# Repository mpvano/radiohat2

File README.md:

# RadioHat 2

This is an early version of the folder full of files that need to be installed on a raspberry pi to allow experimentation with the RadioHat version 2.0 hardware.

When downloading and installing it, ensure that it is named "radiohat2" and that it is in your home directory, or some of the shell scripts it contains will not work properly. When downloaded as a .zip archive, it may result in a folder with the branch suffix "-main" that needs to be removed if you want to use the enclosed shell scripts.

One way to create the folder on a pi is to "cd" to the directory you want it to appear in and then clone the repository using git with the command: "git clone https://github.com/mpvano/radiohat2.git". This will allow you to use all the normal git functionality.

Note also that some of the files in "docs" are very out of date or incomplete. The "Getting Started Guides" refer to a much earlier configuration with different directories on the pi and procedures to set things up. They're presented here only to give some idea what to do. I'll be replacing them with more modern versions as I get to them. RadioHat is still very much a work in progress.

### The RadioHat hardware

Unlike RadioHat 1, RadioHat2 is an open source peripheral board for the Raspberry Pi in a form similar to an extended Pi "hat". Note that this board overhangs the pi USB and Ethernet connectors to match the dimensions of the Pi itself. This means it does not qualify as an official "HAT". It is intended to be a module containing many of the devices that are commonly needed to implement 3-30Mhz radio transmitters and receivers. It may also be used with other micro-controllers that support I2S if they are sufficiently powerful to handle the needed DSP operations.

It contains the following devices:<ol>
	<li>A Freescale SGTL5000 24 bit full duplex 48Khz I2S Audio codec with headset interface</li>
	<li>A Quadrature Switched Demodulator preceded by a 3-32Mhz Band Pass Filter</li>
	<li>A Quadrature Switched Modulator followed by a 32Mhz Low Pass Filter</li>
	<li>An Si5351 I2C controlled clock oscillator configured to provide quadrature clocks for them</li>
	<li>The EEPROM required by the Pi Foundation for "hat" devices</li>
	<li>Three relay controlled low pass filters intended for use after the Modulator to reduce harmonics before an external power amplifier.</li>
 	<li>A Class A Predriver to improve the Modulator drive capabilities and to compensate for filter losses.</li>
	<li>On board analog regulators to provide cleaner power from an optional external source</li>
</ol>

These devices are wired together in the usual way needed for HF radio operation with DSP provided by the Raspberry Pi. For typical operation as a radio transceiver you still need to provide a power amplifier with output filters and a transmit/receive switching mechanism. The usual output low pass filters are adequate for most uses as input filters for the receiver if the T/R switching is done in such a way that they remain inline with the receiver.

The repository now contains another board design of the same size in FAB/txfilters1 which implements a 5 filter LPF/VSWR Meter/TR Relay for stacking with the RadioHat board. Together with your choice of power amplifier this now allows a complete transceiver to be built easily.

Note that the real time clock option and Codec Line input output connection points that were present in Radiohat 1 have been removed. The Radiohat 1 board whose Kicad Folder is still in the repository remains software compatible with this board and although it is no longer under development it remains a viable option for those needing a true "hat" for the pi, or requiring a real time clock. 

There are two different Kicad folders available for RadioHat 2 - they differ primarily in that the one named "radiohat2_QFP32" is compatible with older 32 pin versions of the codec chip instead of the current 20 pin part. They will eventually be merged into a single version.

### Fabrication of boards
RadioHat2 is open sourced hardware licensed via an MIT license and the Gerber files, preliminary BOM and some draft documentation are all part of the project. 

Although a small production run was completed to provide a few boards for use by software developers, there is currently no way to obtain boards other than ordering them from a board manufacturer yourself - this is easy and inexpensive to do and the needed Gerber files are in this repository.

Note that this board is very compact and built with QFPn and 0603 components. It's not very practical to attempt assembly by hand. The board is intended to be reflow soldered after the components are placed on pads with the help of a front side solder paste screen.

### Software
The provided software is a collection of example and test programs that demonstrate operation of the board and allow testing and troubleshooting of it. They are only intended as a starting point for more serious software development. Experimental support is also provided for use with the popular "Quisk" Transceiver software as well.

This repository is newly setup and is still being tested. There may be some issues with missing files, etc. They are being addressed as quickly as possible.

### Dependencies
In general they are confined to the normal Raspberry Pi build tools, with the exception of ncurses and its development tools.

There is a simple installation described in the PDF file in the DOC folder.

Version 7 of Kicad or later is needed to modify the board design.

### Mailing list

There is a moderated mailing list for discussing this project at https://groups.io/g/RadioHat. This project's goal is develop radio equipment that requires a valid radio amateur operator's license to operate. Please include your valid station call sign in requests to join the list, and the nature of your interest in the project.

Mario Vano
AE0GL

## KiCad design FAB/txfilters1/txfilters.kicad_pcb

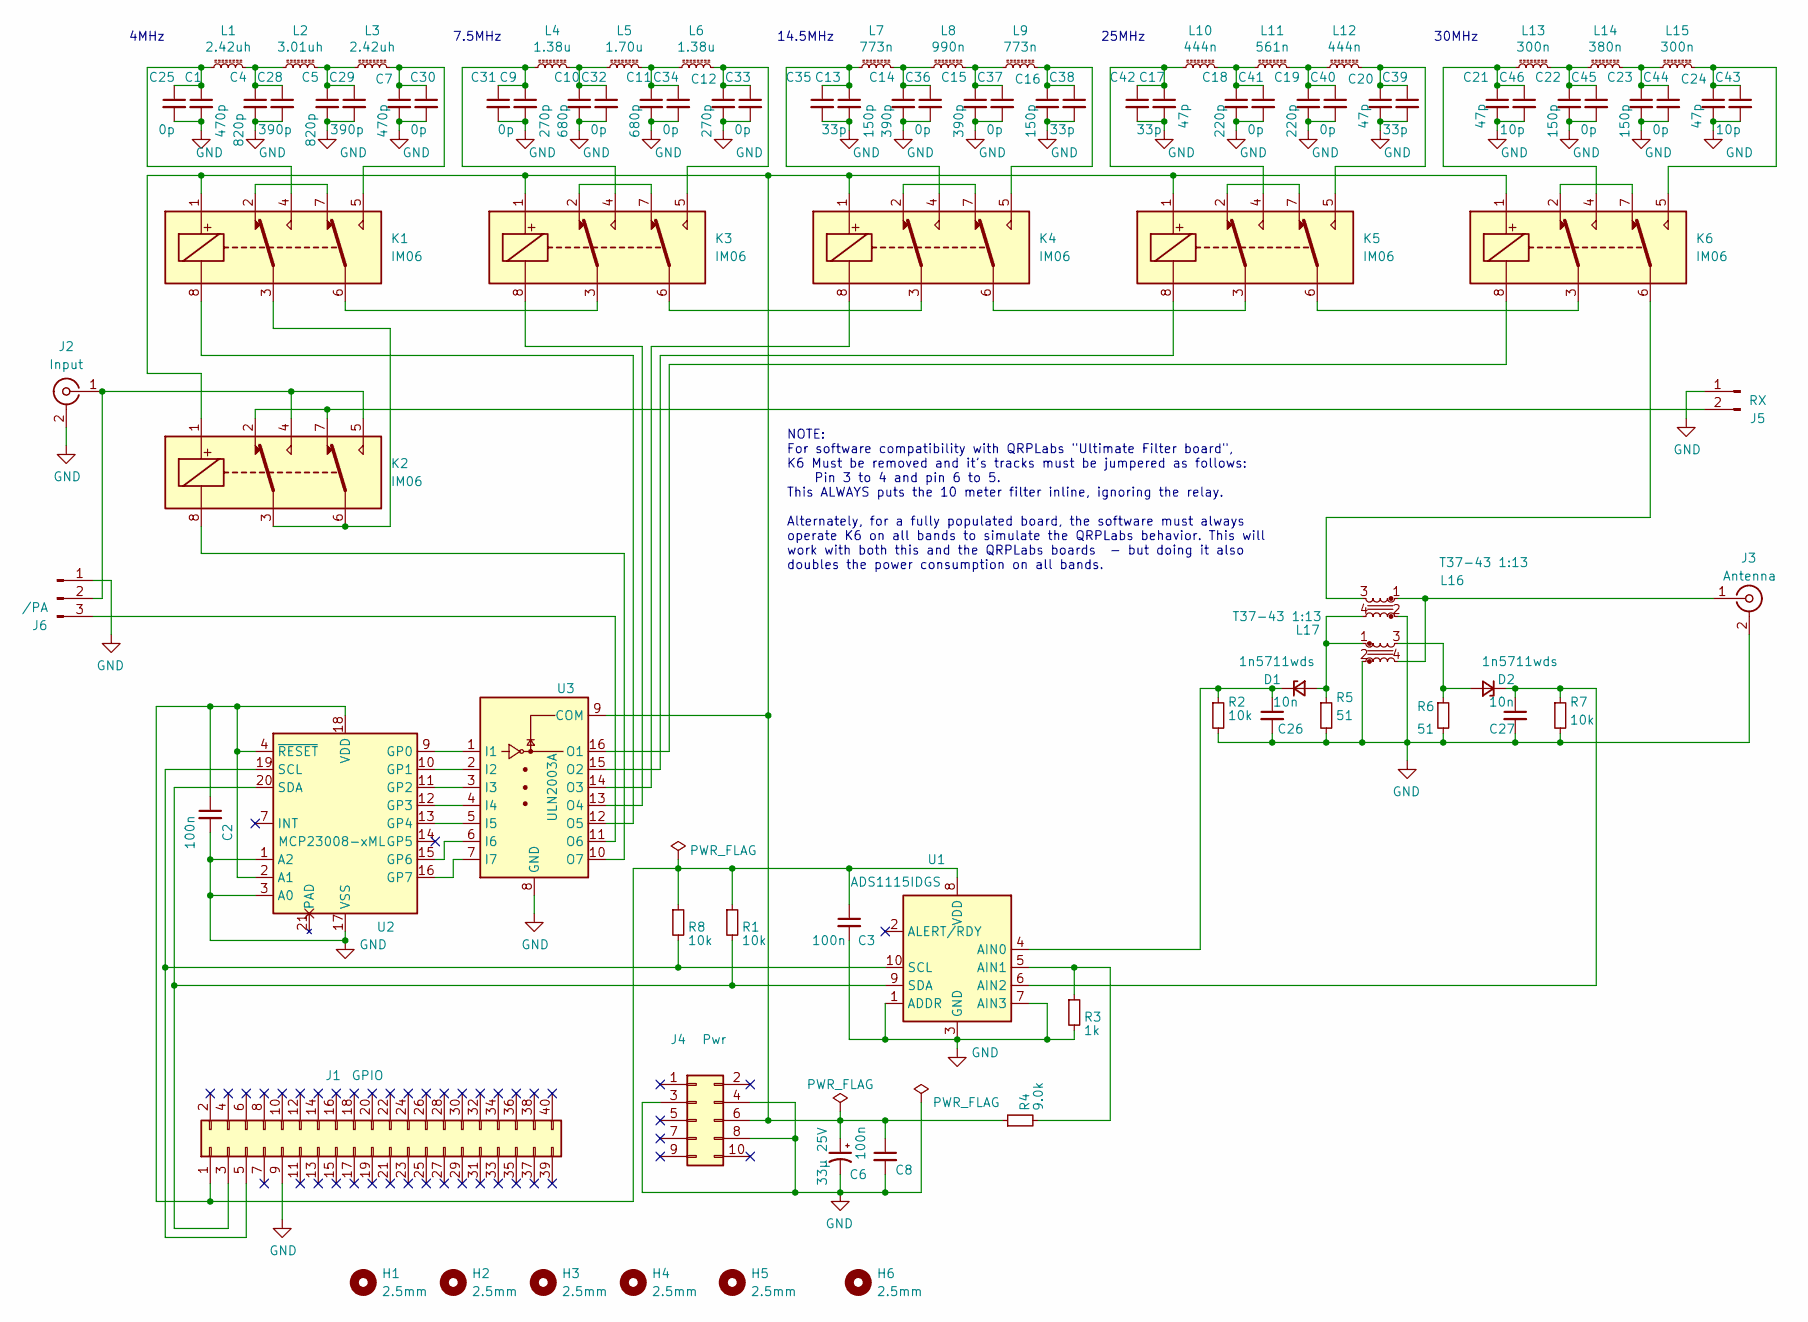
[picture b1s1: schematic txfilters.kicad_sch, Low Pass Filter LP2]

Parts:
C1, C7: 470p; C_1206_3216Metric; Manufacturer_Part_Number KGM31VCG2D471JU; DigiKey Part Number 478-KGM31VCG2D471JUCT-ND
C2, C3, C8: 100n; C_0603_1608Metric; Manufacturer_Part_Number CL10B104JB8NNNC; DigiKey Part Number 1276-1033-1-ND
C4, C5: 820p; C_1206_3216Metric; Manufacturer_Part_Number KGM31VCG2D821JU; DigiKey Part Number 478-KGM31VCG2D821JUCT-ND
C6: 33µ 25V; C_Elec_5x5.8; Manufacturer_Part_Number EEE-FK1E330UR; DigiKey Part Number PCE3802CT-ND
C9, C12: 270p; C_1206_3216Metric; Manufacturer_Part_Number KGM31BCG2D271JT; DigiKey Part Number 478-KGM31BCG2D271JTCT-ND
C10, C11: 680p; C_1206_3216Metric; Manufacturer_Part_Number KGM31VCG2D681JU; DigiKey Part Number 478-KGM31VCG2D681JUCT-ND
C13, C16, C22, C23: 150p; C_1206_3216Metric; Manufacturer_Part_Number KGM31BCG2D151JT; DigiKey Part Number 478-KGM31BCG2D151JTCT-ND
C14, C15, C28, C29: 390p; C_1206_3216Metric; Manufacturer_Part_Number KGM31BCG2D391JT; DigiKey Part Number 478-KGM31BCG2D391JTCT-ND
C17, C20, C21, C24: 47p; C_1206_3216Metric; Manufacturer_Part_Number KGM31BCG2D470JT; DigiKey Part Number 478-KGM31BCG2D470JTCT-ND
C18, C19: 220p; C_1206_3216Metric; Manufacturer_Part_Number KGM31BCG2D221JT; DigiKey Part Number 478-KGM31BCG2D221JTCT-ND
C25, C30, C31, C32, C33, C34, C36, C37, C40, C41, C44, C45: 0p; C_1206_3216Metric
C26, C27: 10n; C_0603_1608Metric; Manufacturer_Part_Number Samsung Electro-Mechanics; DigiKey Part Number 1276-1091-1-ND
C35, C38, C39, C42: 33p; C_1206_3216Metric; Manufacturer_Part_Number KGM31BCG2D330JT; DigiKey Part Number 478-KGM31BCG2D330JTCT-ND
C43, C46: 10p; C_1206_3216Metric; Manufacturer_Part_Number KGM31BCG2D100JT; DigiKey Part Number 478-KGM31BCG2D100JTCT-ND
D1, D2: 1n5711wds; D_SOD-323; Manufacturer_Part_Number 1N5711WS-7-F; DigiKey Part Number 1N5711WS-FDICT-ND
H1, H2, H3, H4, H5, H6: 2.5mm; MountingHole_2.7mm_M2.5_KA
J1: GPIO; PinSocket_2x20_P2.54mm_Vertical
J2: Input; SMA_Amphenol_132289_EdgeMount
J3: Antenna; SMA_Amphenol_132289_EdgeMount
J4: Pwr; PinSocket_2x05_P2.54mm_Vertical
J5: RX; JST_XH_B2B-XH-A_1x02_P2.50mm_Vertical
J6: /PA; JST_XH_B3B-XH-A_1x03_P2.50mm_Vertical
K1, K2, K3, K4, K5, K6: IM06; Relay_DPDT_AXICOM_IMSeries_Pitch5.08mm; Manufacturer_Part_Number 2-1462037; DigiKey Part Number PB1096-ND
L1, L3: 2.42uh; L_Toroid_Vertical_L14.0mm_W6.3mm_P4.57mm_Pulse_A
L2: 3.01uh; L_Toroid_Vertical_L14.0mm_W6.3mm_P4.57mm_Pulse_A
L4, L6: 1.38u; L_Toroid_Vertical_L14.0mm_W6.3mm_P4.57mm_Pulse_A
L5: 1.70u; L_Toroid_Vertical_L14.0mm_W6.3mm_P4.57mm_Pulse_A
L7, L9: 773n; L_Toroid_Vertical_L14.0mm_W6.3mm_P4.57mm_Pulse_A
L8: 990n; L_Toroid_Vertical_L14.0mm_W6.3mm_P4.57mm_Pulse_A
L10, L12: 444n; L_Toroid_Vertical_L14.0mm_W6.3mm_P4.57mm_Pulse_A
L11: 561n; L_Toroid_Vertical_L14.0mm_W6.3mm_P4.57mm_Pulse_A
L13, L15: 300n; L_Toroid_Vertical_L14.0mm_W6.3mm_P4.57mm_Pulse_A
L14: 380n; L_Toroid_Vertical_L14.0mm_W6.3mm_P4.57mm_Pulse_A
L16, L17: T37-43 1:13; Transformer_Toroid_Horizontal_D9.0mm_Amidon-T30
R1, R2, R7, R8: 10k; R_0603_1608Metric; Manufacturer_Part_Number RMCF0603FT10K0; DigiKey Part Number RMCF0603FT10K0CT-ND
R3: 1k; R_0603_1608Metric; Manufacturer_Part_Number RMCF0603FT1K00; DigiKey Part Number RMCF0603FT1K00CT-ND
R4: 9.0k; R_0603_1608Metric; Manufacturer_Part_Number RMCF0603FT9K09; DigiKey Part Number RMCF0603FT9K09CT-ND
R5, R6: 51; R_0603_1608Metric; Manufacturer_Part_Number RMCF0603FT51R0; DigiKey Part Number RMCF0603FT51R0CT-ND
U1: ADS1115IDGS; TSSOP-10_3x3mm_P0.5mm; Manufacturer_Part_Number ADS1115IDGSR; DigiKey Part Number 296-38849-1-ND
U2: MCP23008-xML; QFN-20-1EP_4x4mm_P0.5mm_EP2.7x2.7mm; Manufacturer_Part_Number MCP23008T-E/ML; DigiKey Part Number MCP23008T-E/MLCT-ND
U3: ULN2003A; SOIC-16_3.9x9.9mm_P1.27mm; Manufacturer_Part_Number ULN2003A; DigiKey Part Number 4518-ULN2003ACT-ND

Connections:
GND: C1.2, C2.2, C3.2, C4.2, C5.2, C6.2, C7.2, C8.2, C9.2, C10.2, C11.2, C12.2, C13.2, C14.2, C15.2, C16.2, C17.2, C18.2, C19.2, C20.2, C21.2, C22.2, C23.2, C24.2, C25.2, C26.2, C27.2, C28.2, C29.2, C30.2, C31.2, C32.2, C33.2, C34.2, C35.2, C36.2, C37.2, C38.2, C39.2, C40.2, C41.2, C42.2, C43.2, C44.2, C45.2, C46.2, J1.9, J2.2 (Ext), J3.2 (Ext), J4.3, J4.4, J4.8, J5.1, J6.1, L16.2, L17.2, R2.2, R3.2, R5.2, R6.2, R7.2, U1.1 (ADDR), U1.3 (GND), U1.7 (AIN3), U2.1 (A2), U2.3 (A0), U2.17 (VSS), U3.8 (GND)
unnamed: C1.1, C25.1, K1.4, L1.2
unnamed: C10.1, C32.1, L4.1, L5.2
unnamed: C11.1, C34.1, L5.1, L6.2
unnamed: C12.1, C33.1, K3.5, L6.1
unnamed: C13.1, C35.1, K4.4, L7.2
unnamed: C14.1, C36.1, L7.1, L8.2
unnamed: C15.1, C37.1, L8.1, L9.2
unnamed: C16.1, C38.1, K4.5, L9.1
unnamed: C17.1, C42.1, K5.4, L10.2
unnamed: C18.1, C41.1, L10.1, L11.2
unnamed: C19.1, C40.1, L11.1, L12.2
unnamed: C20.1, C39.1, K5.5, L12.1
unnamed: C21.1, C46.1, K6.4, L13.2
unnamed: C22.1, C45.1, L13.1, L14.2
unnamed: C23.1, C44.1, L14.1, L15.2
unnamed: C24.1, C43.1, K6.5, L15.1
unnamed: C4.1, C28.1, L1.1, L2.2
unnamed: C5.1, C29.1, L2.1, L3.2
unnamed: C7.1, C30.1, K1.5, L3.1
unnamed: C9.1, C31.1, K3.4, L4.2
unnamed: D1.2 (A), L16.4, L17.1, R5.1
unnamed: C26.1, D1.1 (K), R2.1, U1.4 (AIN0)
unnamed: D2.2 (A), L17.3, R6.1
unnamed: C27.1, D2.1 (K), R7.1, U1.6 (AIN2)
unnamed: C2.1, C3.1, J1.1, R1.1, R8.1, U1.8 (VDD), U2.2 (A1), U2.4 (~RESET), U2.18 (VDD)
unnamed: J1.3, R1.2, U1.9 (SDA), U2.20 (SDA)
unnamed: J1.5, R8.2, U1.10 (SCL), U2.19 (SCL)
unnamed: J2.1 (In), J6.2, K2.4, K2.5
unnamed: J3.1 (In), L16.1, L17.4
unnamed: C6.1, C8.1, J4.6, K1.1, K2.1, K3.1, K4.1, K5.1, K6.1, R4.1, U3.9 (COM)
unnamed: J5.2, K2.2, K2.7
unnamed: J6.3, U3.11 (O6)
unnamed: K1.2, K1.7
unnamed: K1.3, K2.3, K2.6
unnamed: K1.6, K3.3
unnamed: K3.2, K3.7
unnamed: K3.6, K4.3
unnamed: K4.2, K4.7
unnamed: K4.6, K5.3
unnamed: K5.2, K5.7
unnamed: K5.6, K6.3
unnamed: K6.2, K6.7
unnamed: K6.6, L16.3
unnamed: R3.1, R4.2, U1.5 (AIN1)
unnamed: U2.9 (GP0), U3.1 (I1)
unnamed: U2.10 (GP1), U3.2 (I2)
unnamed: U2.11 (GP2), U3.3 (I3)
unnamed: U2.12 (GP3), U3.4 (I4)
unnamed: U2.13 (GP4), U3.5 (I5)
unnamed: U2.15 (GP6), U3.6 (I6)
unnamed: U2.16 (GP7), U3.7 (I7)
unnamed: K6.8, U3.16 (O1)
unnamed: K5.8, U3.15 (O2)
unnamed: K4.8, U3.14 (O3)
unnamed: K3.8, U3.13 (O4)
unnamed: K1.8, U3.12 (O5)
unnamed: K2.8, U3.10 (O7)

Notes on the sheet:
30MHz
7.5MHz
25MHz
4MHz
14.5MHz
NOTE: For software compatibility with QRPLabs "Ultimate Filter board", K6 Must be removed and it's tracks must be jumpered as follows: Pin 3 to 4 and pin 6 to 5. This ALWAYS puts the 10 meter filter inline, ignoring the relay. Alternately, for a fully populated board, the software must always opera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

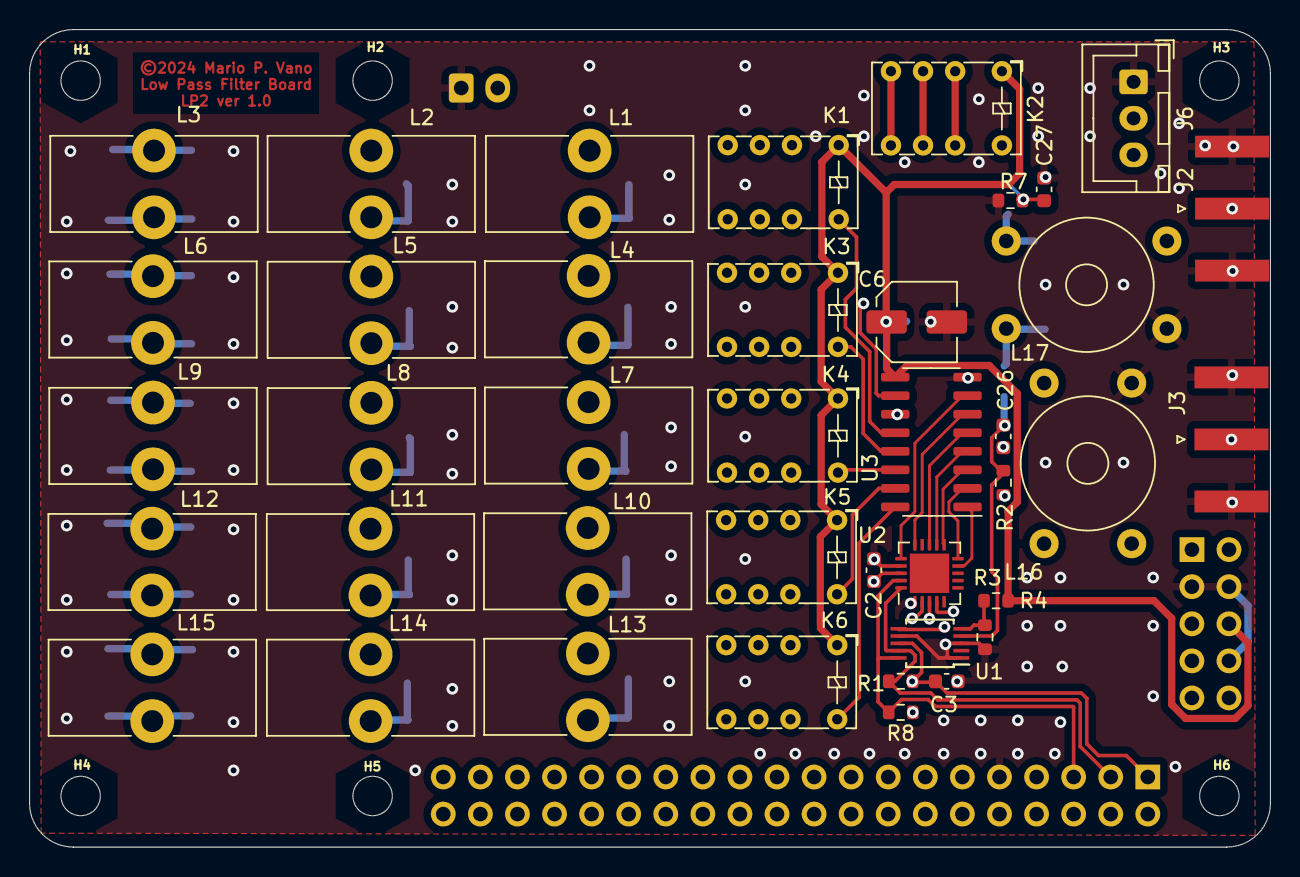
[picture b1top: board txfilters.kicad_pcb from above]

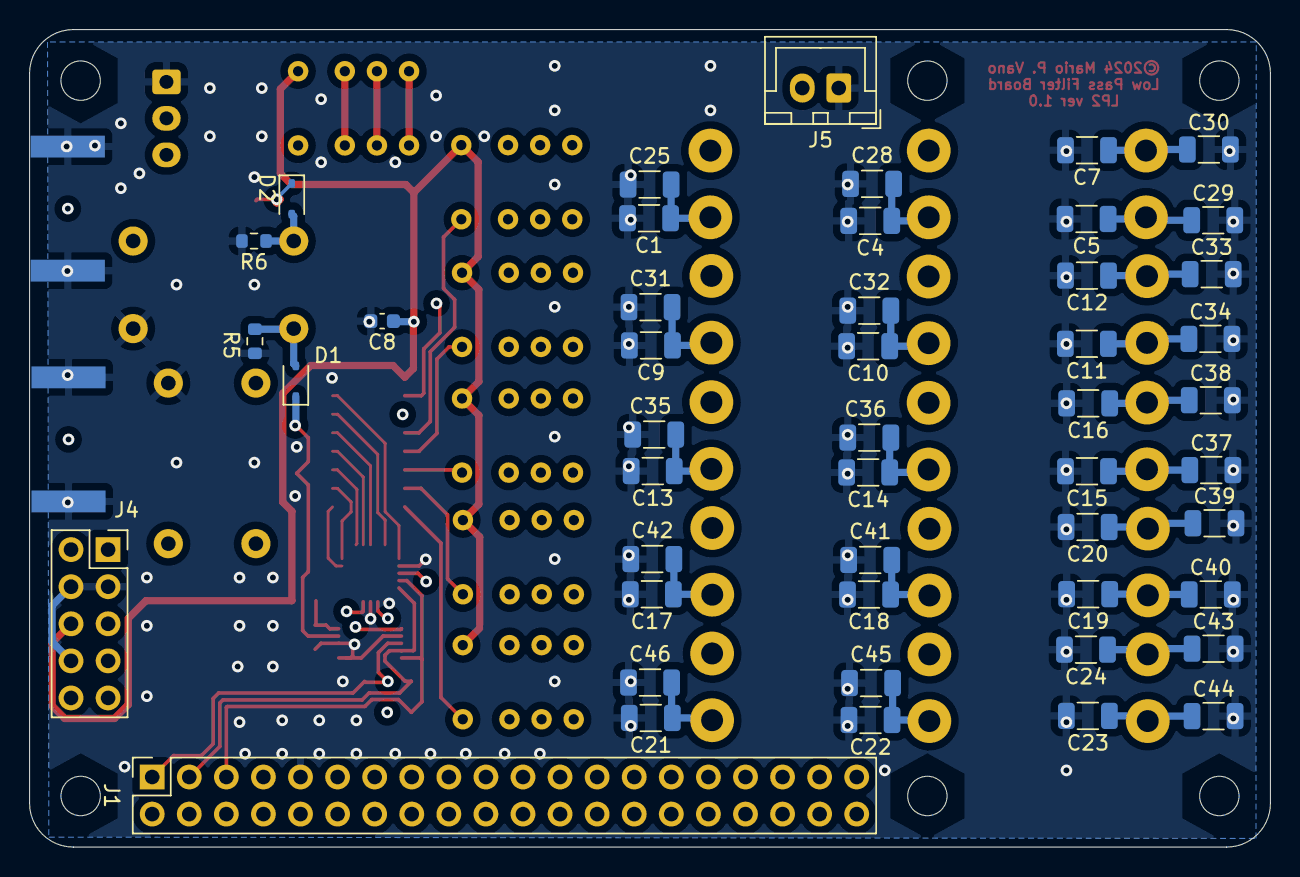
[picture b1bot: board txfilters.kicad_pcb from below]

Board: 4 copper layers, 85.0 x 56.0 mm, 94 parts (48 on the bottom side), 58 nets.

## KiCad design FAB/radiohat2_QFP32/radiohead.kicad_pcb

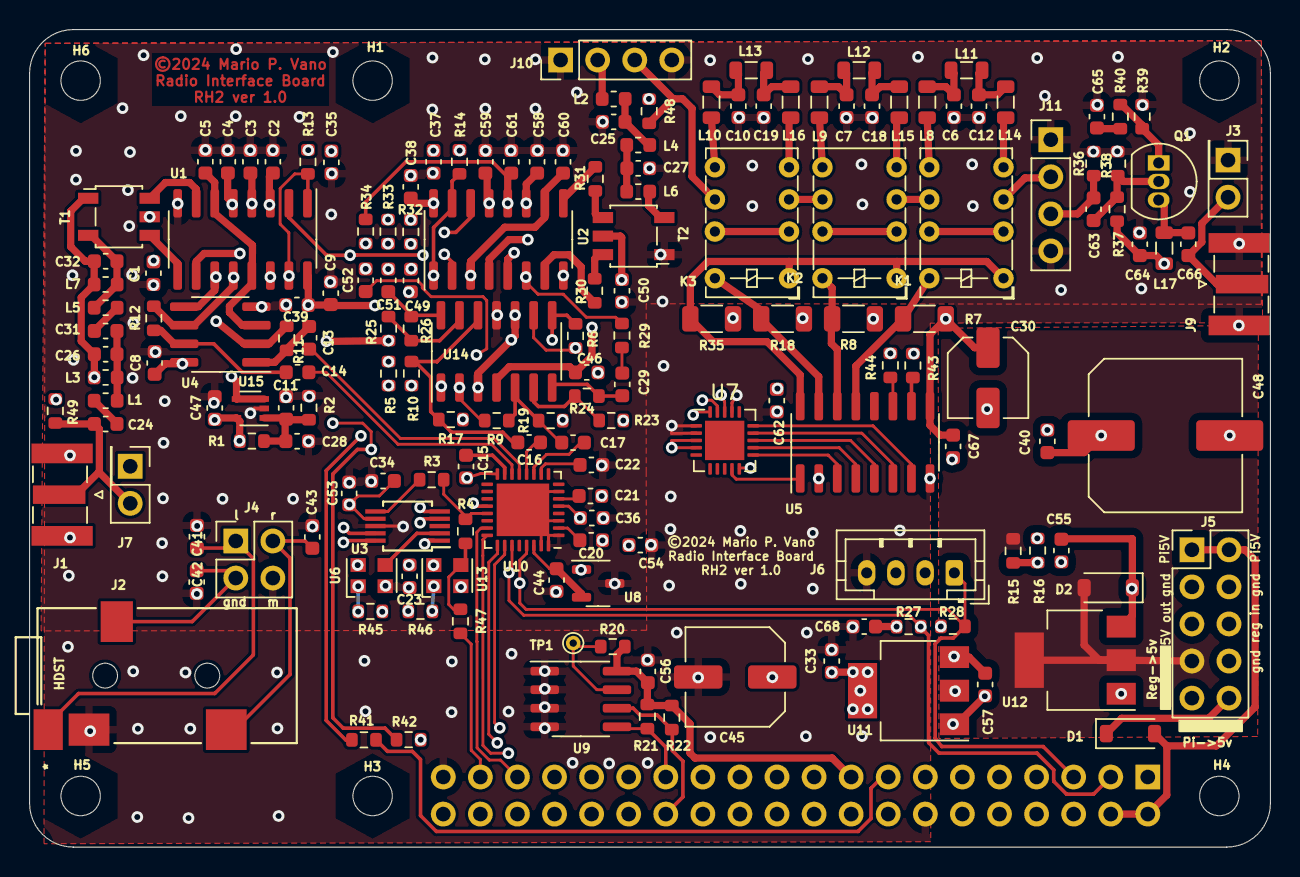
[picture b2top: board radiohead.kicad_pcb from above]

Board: 4 copper layers, 85.0 x 56.0 mm, 175 parts (1 on the bottom side), 124 nets.

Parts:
C1, C50: 10n; C_0603_1608Metric
C2, C3, C4, C5: 470n; C_0603_1608Metric
C6, C12: 200p; C_0603_1608Metric
C7, C18: 360p; C_0603_1608Metric
C8, C9, C22, C23, C28, C33, C34, C35, C36, C37, C38, C39, C46, C47, C54, C55, C56, C57, C62, C63, C64, C66, C67, C68: 100n; C_0603_1608Metric
C10, C19: 750p; C_0603_1608Metric
C11, C29, C40, C49, C51, C52, C53: 10µ; C_0603_1608Metric
C13, C14, C15, C16, C17, C20, C21, C44: 1µ; C_0603_1608Metric
C24, C31: 620p; C_0603_1608Metric
C25, C27: 130p; C_0603_1608Metric
C26, C32: 180p; C_0603_1608Metric
C30: 33µ 25V; C_Elec_5x5.8
C41, C42, C43, C65: 1n; C_0603_1608Metric
C45: 100µ 5V; C_Elec_6.3x5.4
C48: 1500µ 6.3V; C_Elec_10x10.2
C58, C59, C60, C61: 22n; C_0603_1608Metric
D1, D2: 20V 500MA; D_SOD-123
H1, H2, H3, H4, H5, H6: 2.5mm; MountingHole_2.7mm_M2.5_KA
J1: RF In; SMA_Samtec_SMA-J-P-X-ST-EM1_EdgeMount
J2: HDST; SJ-43514TS-SMT
J3: RF out; PinHeader_2x01_P2.54mm_Vertical
J4: Headset; PinHeader_2x02_P2.54mm_Vertical
J5: Power; PinHeader_2x05_P2.54mm_Vertical
J6: STEMMA I2C; JST_PH_B4B-PH-K_1x04_P2.00mm_Vertical
J7: RF In; PinHeader_2x01_P2.54mm_Vertical
J8: Raspberry Pi GPIO; PinSocket_2x20_P2.54mm_Vertical
J9: RF out B; SMA_Samtec_SMA-J-P-X-ST-EM1_EdgeMount
J10: QSD | LPF; PinHeader_1x04_P2.54mm_Vertical
J11: LPF | PA; PinHeader_1x04_P2.54mm_Vertical
K1, K2, K3: IM43; Relay_DPDT_AXICOM_IMSeries_Pitch5.08mm
L1, L2, L5, L6: 470n; L_0603_1608Metric
L3, L7: 1µ5; L_0603_1608Metric
L4: 560n; L_0603_1608Metric
L8, L14: 560n; L_0805_2012Metric
L9, L11, L15: 820n; L_0805_2012Metric
L10, L12, L16: 1µ5; L_0805_2012Metric
L13: 2µ7; L_0805_2012Metric
L17: 40µ; L_0805_2012Metric
Q1: PN2222A; TO-92_Inline
R1: 12k; R_0603_1608Metric
R2, R24, R26: 20k; R_0603_1608Metric
R3, R4, R41, R42, R43, R44, R47, R48, R49: 0r; R_0603_1608Metric
R5, R6: 30k; R_0603_1608Metric
R7, R8, R18, R35: 350R; R_1206_3216Metric
R9, R10, R11, R12, R13, R14, R17, R19, R23, R25, R27, R28, R45, R46: 10k; R_0603_1608Metric
R15: 333r; R_0603_1608Metric
R16, R20: 1k; R_0603_1608Metric
R21, R22: 3k9; R_0603_1608Metric
R29, R30, R31, R32, R33, R34, R36, R39: 50R; R_0603_1608Metric
R37: 2k2; R_0603_1608Metric
R38: 450R; R_0603_1608Metric
R40: 68R; R_0603_1608Metric
T1, T2: MABAES0031; Transformer_MACOM_MABAES00031CT
TP1: /Write; TestPoint_THTPad_D1.0mm_Drill0.5mm
U1, U2: SN74CBT3253; SOIC-16_3.9x9.9mm_P1.27mm
U3: Si5351A-B-GT; MSOP-10_3x3mm_P0.5mm
U4: LM4562; SOIC-8_3.9x4.9mm_P1.27mm
U5: ULN2003A; SOIC-16_3.9x9.9mm_P1.27mm
U6: tcxo 25.0Mhz; Oscillator_SMD_Kyocera_KC2520Z-4Pin_2.5x2.0mm
U7: MCP23008-xML; QFN-20-1EP_4x4mm_P0.5mm_EP2.7x2.7mm
U8: ap7313; SOT-23-3
U9: CAT24C128; SOIC-8_3.9x4.9mm_P1.27mm
U10: SGTL5000XNAA3; QFN-32-1EP_5x5mm_P0.5mm_EP3.6x3.6mm
U11: LD1117S33TR_SOT223; SOT-223-3_TabPin2
U12: LM317_SOT-223; SOT-223-3_TabPin2
U13: txco 12.288Mhz; Oscillator_SMD_Kyocera_KC2520Z-4Pin_2.5x2.0mm
U14: TLV9064; SO-14_3.9x8.65mm_P1.27mm
U15: TLV9001IDCK; SOT-353_SC-70-5

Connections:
+3V3: C56.1, C68.1, J6.3, J8.1, J8.17, R20.2, R21.2, R22.2, R27.2, R28.2, U9.8 (VCC)
+5V: C8.1, C9.1, C38.1, C39.1, C40.2, C46.1, C48.1, C57.1, J5.5, J5.9, U1.16 (VCC), U2.16 (VCC), U4.8 (V+), U11.3 (VI), U14.4 (V+)
+12V: C30.1, C55.1, C64.1, C67.1, D2.1 (K), J5.6, L17.1, R7.1, R8.1, R18.1, R35.1, R37.1, U5.9 (COM), U12.3 (VI)
/T_MCLK: J8.37, R47.2
BIAS2V: C1.1, C50.1, R17.1, R19.2, R23.2, R25.2, T1.2, T2.2, U14.3 (+), U14.10 (+), U15.3 (-), U15.4
CODEC-DIN: J8.40, U10.26 (I2S_DIN)
CODEC-DOUT: J8.38, U10.25 (I2S_DOUT)
CODEC-LRCLK: J8.35, U10.23 (I2S_LRCLK)
CODEC-SCLK: J8.12, U10.24 (I2S_SCLK)
CODEC_MCLK: R3.2, R4.2, U10.21 (SYS_MCLK)
GND: C1.2, C2.2, C3.2, C4.2, C5.2, C6.2, C7.2, C8.2, C9.2, C10.2, C11.2, C12.2, C18.2, C19.2, C22.1, C23.1, C25.2, C27.2, C28.2, C30.2, C33.2, C34.2, C35.2, C36.2, C37.2, C38.2, C39.2, C40.1, C41.1, C42.1, C43.1, C44.1, C45.2, C46.2, C47.2, C48.2, C50.2, C53.1, C54.2, C55.2, C56.2, C57.2, C58.2, C59.2, C60.2, C61.2, C62.2, C64.2, C65.2, C67.2, C68.2, J2.4, J3.1, J4.4, J5.3, J5.4, J5.8, J6.4, J8.6, J8.9, J8.14, J8.20, J8.25, J8.30, J8.34, J8.39, J9.2 (Ext), J10.1, J10.4, J11.1, J11.4, R2.1, R16.2, R36.2, R38.2, R39.2, T2.4, U1.8 (GND), U2.8 (GND), U3.8 (GND), U4.4 (V-), U5.8 (GND), U6.2 (GND), U7.1 (A2), U7.2 (A1), U7.17 (VSS), U8.3 (GND), U9.1 (A0), U9.2 (A1), U9.3 (A2), U9.4 (GND), U10.1 (GND), U10.3 (GND), U10.7 (AGND), U10.31 (CTRL_ADR0_CS), U10.32 (CTRL_MODE), U10.33 (GND), U11.1 (GND), U13.2 (GND), U14.11 (V-), U15.2 (V-)
HPL: C21.1, C43.2, J2.2, J4.2
HPR: C20.1, C41.2, J2.3, J4.3
I2C-SCL: J6.1, J8.5, R28.1, U3.4 (SCL), U7.19 (SCL), U10.29 (CTRL_CLK)
I2C-SDA: J6.2, J8.3, R27.1, U3.5 (SDA), U7.20 (SDA), U10.27 (CTRL_DATA)
LINEIN-L: C14.1, U10.14 (LINEIN_L)
LINEIN-R: C13.2, U10.13 (LINEIN_R)
LINEOUT_L: C16.1, R10.1, R17.2, U14.12 (+)
LINEOUT_R: C17.2, R9.1, R19.1, U14.5 (+)
MIC-IN: C15.1, C42.2, J2.1, J4.1, U10.16 (MIC_BIAS)
unnamed: C6.1, L8.1, L11.2
unnamed: C7.1, L9.1, L12.2
unnamed: C10.1, L10.1, L13.2
unnamed: C12.1, L11.1, L14.1
unnamed: C13.1, R11.1, U4.1
unnamed: C14.2, R12.1, U4.7
unnamed: C18.1, L12.1, L15.1
unnamed: C19.1, L13.1, L16.1
unnamed: C24.1, L1.2
unnamed: C25.1, L2.1, L4.2
unnamed: C26.1, C31.2, L1.1, L3.1
unnamed: C27.1, L4.1, L6.2
unnamed: C29.1, R24.2, U14.7
unnamed: C29.2, R29.1
unnamed: C31.1, L5.2
unnamed: C32.1, L5.1, L7.1, T1.5
unnamed: C49.1, R5.2, U14.1
unnamed: C49.2, R32.1
unnamed: C51.1, R26.2, U14.14
unnamed: C51.2, R33.1
unnamed: C52.1, R6.2, U14.8
unnamed: C52.2, R34.1
unnamed: C65.1, R40.2
unnamed: D1.2 (A), J5.1, J5.2, J8.2, J8.4
unnamed: D1.1 (K), J5.10
unnamed: D2.2 (A), J5.7, R15.1, U12.2 (VO)
unnamed: C26.2, C32.2, J1.2 (Ext), J7.1, L3.2, L7.2, T1.4
unnamed: C24.2, J1.1 (In), J7.2, R49.1
unnamed: C66.2, J3.2, J9.1 (In)
unnamed: J8.15, R41.2
unnamed: J8.16, R42.2
unnamed: J8.27, R21.1, U9.5 (SDA)
unnamed: J8.28, R22.1, U9.6 (SCL)
unnamed: J10.3, K3.6, R48.2
unnamed: J11.2, K1.3
unnamed: C63.2, J11.3, R36.1
unnamed: K1.2, K1.7
unnamed: K1.4, L14.2
unnamed: K1.5, L8.2
unnamed: K1.6, K2.3
unnamed: K2.2, K2.7
unnamed: K2.4, L15.2
unnamed: K2.5, L9.2
unnamed: K2.6, K3.3
unnamed: K3.2, K3.7
unnamed: K3.4, L16.2
unnamed: K3.5, L10.2
unnamed: L6.1, T2.5
unnamed: C63.1, Q1.2 (B), R37.2, R38.1
unnamed: C66.1, L17.2, Q1.3 (C)
unnamed: Q1.1 (E), R39.1, R40.1
unnamed: R30.2, T2.1
unnamed: R31.2, T2.3
unnamed: T1.1, U1.7 (1A)
unnamed: C5.1, U1.6 (1B1), U1.13 (2B4), U4.3 (+)
unnamed: C4.1, R12.2, U1.5 (1B2), U1.12 (2B3), U4.6 (-)
unnamed: C3.1, U1.4 (1B3), U1.11 (2B2), U4.5 (+)
unnamed: C2.1, R11.2, U1.3 (1B4), U1.10 (2B1), U4.2 (-)
unnamed: T1.3, U1.9 (2A)
unnamed: R30.1, U2.7 (1A)
unnamed: C59.1, R29.2, U2.6 (1B1), U2.13 (2B4)
unnamed: C61.1, R34.2, U2.5 (1B2), U2.12 (2B3)
unnamed: C58.1, R33.2, U2.4 (1B3), U2.11 (2B2)
unnamed: C60.1, R32.2, U2.3 (1B4), U2.10 (2B1)
unnamed: R31.1, U2.9 (2A)
unnamed: R3.1, U3.6 (CLK2)
unnamed: U3.2 (XA), U6.3 (CLK)
unnamed: U5.1 (I1), U7.9 (GP0)
unnamed: U5.2 (I2), U7.10 (GP1)
unnamed: U5.3 (I3), U7.11 (GP2)
unnamed: U5.4 (I4), U7.12 (GP3)
unnamed: U5.5 (I5), U7.13 (GP4)
unnamed: U5.6 (I6), U7.14 (GP5)
unnamed: U5.7 (I7), U7.15 (GP6)
unnamed: K1.1, K2.1, K3.1, R35.2, U5.16 (O1)
unnamed: K3.8, R18.2, U5.15 (O2)
unnamed: K2.8, R8.2, U5.14 (O3)
unnamed: K1.8, R7.2, U5.13 (O4)
unnamed: R44.2, U5.11 (O6)
unnamed: R43.2, U5.10 (O7)
unnamed: R45.2, U6.1 (INH)
unnamed: R20.1, TP1.1, U9.7 (WP)
unnamed: C21.2, U10.6 (HP_L)
unnamed: C20.2, U10.2 (HP_R)
unnamed: C16.2, U10.12 (LINEOUT_L)
unnamed: C17.1, U10.11 (LINEOUT_R)
unnamed: C15.2, U10.15 (MIC)
unnamed: C22.2, U10.10 (VAG)
unnamed: C44.2, U8.2 (VO), U10.30 (VDDD)
unnamed: R15.2, R16.1, U12.1 (ADJ)
unnamed: R46.2, U13.1 (INH)
unnamed: R5.1, R9.2, U14.2 (-)
unnamed: R23.1, R24.1, U14.6 (-)
unnamed: R6.1, R10.2, U14.9 (-)
unnamed: R25.1, R26.1, U14.13 (-)
unnamed: C11.1, C28.1, R1.1, R2.2, U15.1 (+)
PRE-IN: J10.2, L2.2
RX-INBUS: R48.1, R49.2
TEENSY: R4.1, R47.1, U13.3 (CLK)
VCC: C23.2, C33.1, C34.1, C35.1, C36.1, C37.1, C45.1, C47.1, C53.2, C54.1, C62.1, R1.2, R13.2, R14.2, R45.1, R46.1, U3.1 (VDD), U3.7 (VDDO), U6.4 (VCC), U7.3 (A0), U7.4 (~RESET), U7.18 (VDD), U8.1 (VI), U10.5 (VDDA), U10.20 (VDDIO), U11.2 (VO), U13.4 (VCC), U15.5 (V+)
VFO-S0: U1.14 (S0), U2.14 (S0), U3.10 (CLK0)
VFO-S1: U1.2 (S1), U2.2 (S1), U3.9 (CLK1)
/RX-EN: R13.1, R42.1, R44.1, U1.1 (1~OE), U1.15 (2~OE)
/TX-EN: R14.1, R41.1, R43.1, U2.1 (1~OE), U2.15 (2~OE)

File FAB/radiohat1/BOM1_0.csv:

Reference, Quantity, Value, Footprint, Datasheet, Description, Height, Manufacturer_Name, Manufacturer_Part_Number, Mouser Part Number, Mouser Price/Stock
C1 C50,2,10n,Capacitor_SMD:C_0603_1608Metric,~,,,,,,
C12 C13 C14 C15 C16 C17 C18 C19 C20 C21 C30 C44,12,1m,Capacitor_SMD:C_0603_1608Metric,~,,,,,,
C8 C9 C10 C22 C23 C33 C34 C35 C36 C37 C38 C39 C46 C47 C54 C56 C57,17,100n,Capacitor_SMD:C_0603_1608Metric,~,,,,,,
C25 C27,2,130p,Capacitor_SMD:C_0603_1608Metric,~,,,,,,
C26 C32,2,180p,Capacitor_SMD:C_0603_1608Metric,~,,,,,,
C11 C28 C40 C53,4,10m,Capacitor_SMD:C_0603_1608Metric,~,,,,,,
C24 C31,2,620p,Capacitor_SMD:C_0603_1608Metric,~,,,,,,
C41 C42 C43,3,1n,Capacitor_SMD:C_0603_1608Metric,~,,,,,,
C45,1,100m,Capacitor_SMD:C_Elec_6.3x5.4,~,,,,,,
C48,1,1500m,Capacitor_SMD:C_Elec_10x10.2,~,,,,,,
C29 C49 C51 C52,4,10u,Capacitor_SMD:C_0603_1608Metric,~,,,,,,
C2 C3 C4 C5,4,470n,Capacitor_SMD:C_0603_1608Metric,~,,,,,,
C55,1,100n 25V,Capacitor_SMD:C_0603_1608Metric,~,,,,,,
C58 C59 C60 C61,4,22n,Capacitor_SMD:C_0603_1608Metric,~,,,,,,
C6 C7,2,4.7n,Capacitor_SMD:C_0603_1608Metric,~,,,,,,
D1,1,MBRA340T3G,radiohead:D_SMA-SMB_Universal_Handsoldering,https://www.onsemi.com/pub/Collateral/MBRA340T3-D.PDF,,,,,,
D2,1,MBR0520LT,Diode_SMD:D_SOD-123,http://www.onsemi.com/pub_link/Collateral/MBR0520LT1-D.PDF,,,,,,
H1 H2 H3 H4,4,2.5mm,MountingHole:MountingHole_2.7mm_M2.5,~,,,,,,
J1,1,HF IN,Connector_Coaxial:SMA_Samtec_SMA-J-P-X-ST-EM1_EdgeMount, ~,,,,,,
J2,1,HF OUT,Connector_Coaxial:SMA_Samtec_SMA-J-P-X-ST-EM1_EdgeMount, ~,,,,,,
J3,1,headset,Connector_Audio:SJ-43514TS-SMT,,,,,,,
J4,1,Headset & I/Q,Connector_PinHeader_2.54mm:PinHeader_2x05_P2.54mm_Vertical,~,,,,,,
J5,1,Power,Connector_PinHeader_2.54mm:PinHeader_2x05_P2.54mm_Vertical,~,,,,,,
J6,1,CR1220,2895:2895,https://www.mouser.com/datasheet/2/215/Keystone_Electronics_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,Coin Cell Battery Holders CR1220 COIN CELL THM RETAINER,2.95,Keystone Electronics,2895,534-2895,https://www.mouser.co.uk/ProductDetail/Keystone-Electronics/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
J7,1,I2C,Connector_JST:JST_PH_S4B-PH-SM4-TB_1x04-1MP_P2.00mm_Horizontal,~,,,,,,
J8,1,Raspberry Pi GPIO,Connector_PinSocket_2.54mm:PinSocket_2x20_P2.54mm_Vertical,~,,,,,,
JP1,1,/TX,Jumper:SolderJumper-2_P1.3mm_Bridged2Bar_Pad1.0x1.5mm,~,,,,,,
JP2,1,/RX,Jumper:SolderJumper-2_P1.3mm_Bridged2Bar_Pad1.0x1.5mm,~,,,,,,
L1 L2 L5 L6,4,470n,Inductor_SMD:L_0603_1608Metric,~,,,,,,
L3 L7,2,1µ5,Inductor_SMD:L_0603_1608Metric,~,,,,,,
L4,1,560n,Inductor_SMD:L_0603_1608Metric,~,,,,,,
R1,1,300,Resistor_SMD:R_0603_1608Metric,~,,,,,,
R9 R10 R11 R12 R13 R14 R17 R18 R19 R23 R25 R27 R28,13,10k,Resistor_SMD:R_0603_1608Metric,~,,,,,,
R15,1,333r,Resistor_SMD:R_0603_1608Metric,~,,,,,,
R2,1,200,Resistor_SMD:R_0603_1608Metric,~,,,,,,
R16 R20,2,1k,Resistor_SMD:R_0603_1608Metric,~,,,,,,
R21 R22,2,3k9,Resistor_SMD:R_0603_1608Metric,~,,,,,,
R24 R26,2,20k,Resistor_SMD:R_0603_1608Metric,~,,,,,,
R3 R4 R7 R8,4,50,Resistor_SMD:R_0603_1608Metric,~,,,,,,
R29 R30 R31 R32 R33 R34,6,50R,Resistor_SMD:R_0603_1608Metric,~,,,,,,
R35,1,0,Resistor_SMD:R_0603_1608Metric,~,,,,,,
R5 R6,2,30k,Resistor_SMD:R_0603_1608Metric,~,,,,,,
T1 T2,2,MABAES0031,radiohead:Transformer_MACOM_MABAES00031CT-HYBRID,https://cdn.macom.com/datasheets/MABAES0060.pdf,Audio Transformers / Signal Transformers .3-200MHz IL 1.5dB Impedance Ratio 1:4,3.8,MACOM,MABAES0031CT,1464-MABAES0031-CT,
TP1,1,/Write,TestPoint:TestPoint_THTPad_D1.0mm_Drill0.5mm,~,,,,,,
TP2,1,I,TestPoint:TestPoint_THTPad_D1.0mm_Drill0.5mm,~,,,,,,
TP3,1,Q,TestPoint:TestPoint_THTPad_D1.0mm_Drill0.5mm,~,,,,,,
TP4,1,MCLK,TestPoint:TestPoint_THTPad_D1.0mm_Drill0.5mm,~,,,,,,
TP5,1,-in,TestPoint:TestPoint_THTPad_D1.0mm_Drill0.5mm,~,,,,,,
TP6,1,+in,TestPoint:TestPoint_THTPad_D1.0mm_Drill0.5mm,~,,,,,,
TP7,1,-out,TestPoint:TestPoint_THTPad_D1.0mm_Drill0.5mm,~,,,,,,
TP8,1,+out,TestPoint:TestPoint_THTPad_D1.0mm_Drill0.5mm,~,,,,,,
TP9,1,RESET,TestPoint:TestPoint_THTPad_D1.0mm_Drill0.5mm,~,,,,,,
U10,1,SGTL5000XNAA3,Package_DFN_QFN:QFN-32-1EP_5x5mm_P0.5mm_EP3.7x3.7mm,https://www.nxp.com/docs/en/data-sheet/SGTL5000.pdf,,,,,,
U11,1,LD1117S33TR_SOT223,Package_TO_SOT_SMD:SOT-223-3_TabPin2,http://www.st.com/st-web-ui/static/active/en/resource/techni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,,,,,,
U12,1,LM317_SOT-223,Package_TO_SOT_SMD:SOT-223-3_TabPin2,http://www.ti.com/lit/ds/symlink/lm317.pdf,,,,,,
U1 U2,2,SN74CBT3253,Package_SO:SOIC-16_3.9x9.9mm_P1.27mm,http://www.ti.com/lit/gpn/sn74cbt3253,,,,,,
U3,1,Si5351A-B-GT,Package_SO:MSOP-10_3x3mm_P0.5mm,https://www.silabs.com/documents/public/data-sheets/Si5351-B.pdf,,,,,,
U4,1,LM4562,Package_SO:SOIC-8_3.9x4.9mm_P1.27mm,http://www.ti.com/lit/ds/symlink/lm4562.pdf,,,,,,
U5 U7,2,TLV2462CDR,Package_SO:SOIC-8_3.9x4.9mm_P1.27mm,http://www.ti.com/lit/ds/symlink/lm358.pdf,,,,,,
U6,1,DS3231MZ,Package_SO:SOIC-8_3.9x4.9mm_P1.27mm,http://datasheets.maximintegrated.com/en/ds/DS3231M.pdf,,,,,,
U8,1,ap7313-18mpv,ul_AP731318SAG7:AP7313-18SAG-7,,,,,,,
U9,1,CAT24C128,Package_SO:SOIC-8_3.9x4.9mm_P1.27mm,https://www.onsemi.com/pub/Collateral/CAT24C128-D.PDF,,,,,,
Y1,1,27Mhz,Crystal:Crystal_SMD_Abracon_ABM8G-4Pin_3.2x2.5mm,~,,,,,,

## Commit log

2024-03-22 RADIOHAT2
2024-03-22 Update .DS_Store
    Initial Upload
2024-03-22 updated readme
    updated readme info
2024-03-22 License updated
2024-03-22 polarity bug on /tx and /rx
2024-03-26 DOC updates
2024-03-26 fab files added
2024-03-26 housekeeping
2024-03-27 Update .gitignore
    pruning unneeded backups
2024-03-27 cleanup
2024-03-27 added QFP32 HW version
2024-03-27 more cleanup
2024-03-27 added transceiver example
2024-03-27 Transceiver formatting
2024-03-27 more detail added
2024-03-27 Correct signal colors
2024-03-28 FOOTPRINT ERROR WARNING
2024-04-20 vfoinit fixed on pi 5
2024-05-02 LPF Board Initial Version
    Kicad Files as sent to Fab for the LPF. VSWR Bridge and T/R Relay designed for stacking with RadioHat2
2024-05-02 updated reference transceiver
    Updated PDF of reference transceiver
2024-05-02 Update Radiohat 2 Reference Transceiver.pdf
    Brought top page reference transceiver image up to date
2024-05-04 updated ref transceiver
2024-05-05 Update vswr.cpp to fix turns ratio scaling bug
    The turns ratio coefficient was not being applied to the diode correction in the power calculations
2024-05-05 Reference Transceiver updated
    Better picture of latest case refurbishment - shows wiring details
2024-05-05 Update hardware_radiohat1.py to metering ON
2024-05-06 more VSWR fixes
    Yes, it's confusing and messy, but now the algorithm agrees with those used by all my other VSWR implementations.
2024-05-06 control.cpp: changed LPF2 limit from 25 to 23Mhz
2024-11-20 Updates from Field
    Updates to the repository based on field experiences with two Display10 reference transceivers
2024-11-22 new script for digital modes
    added socat script to allow gnuradio program "usbplus.py" to work directly with "transceiver" cat emulation and alsa redirection for fldigi and wsjtx
2024-11-26 update quisk settings samples
2024-11-27 updated cat script
2024-11-27 always use ALSA Loopback for digital
2024-12-01 added no-ui version of digital modes
2024-12-01 fix typo in tx filter block
2024-12-14 Added experimental keyer
    An experimental Keyer written in Python was added

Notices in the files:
FAB/radiohat2_QFP32/radiohead.kicad_pcb:
©2024 Mario P. Vano
FAB/txfilters1/txfilters.kicad_sch:
©2024 Mario P. Vano Low Pass Filter Board LP2 ver 1.0
parts and their libraries:
Copyright 2016 Accelerated Designs. All rights reserved.
